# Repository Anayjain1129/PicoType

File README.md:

# PicoType 

## Zine Page

## Physically Built

### What is this project? 
This is a keyboard made from scratch made by a teenage, made from PCB, CAD to firmware everything! basically this is a keyboard which helps you type things and uses RP2040 and and it sounds thockyy!! 

### How to use it?
1. Assemble the PCB by soldering the Raspberry pi pico, switches and encoder and the OLED display which is on the numpad pcb
2. Plug the MCU (raspberry pi pico) with your computer and make sure the boot button on the MCU is pressed down while you are plugging in the MCU
3. Drag and drop the .uf2 file in the MCU of Raspberry Pi Pico 
4. Do the same things with Xiao rp2040
5. wolla you have everything working!! 

### Why did i made this? 
I made this to learn new skills and learn more about PCBs and do ALOT of CAD the case/CAD of this project took so much time! and the case makes it looks so much awesome! and i have made a separate numpad which can alsop be used as a macropad, you can use it as a full sized keyboard or just as a ANSI-75 Keyboard with a small macropad on your desk! the numpad also have a keychian holder so you can carry it easily too! 

# Features
- EC11 Rotary Encoder - For Volume, Brightness etc
- Oled screen -  To play gifs and notifications
- ANSI-75 Layout
- Raspberry Pi Pico
- Custom Layout
- QMK firmware
- Awesome CAD/cool case design
- Uses RP2040

## Schematics 

## PCB

## 3d PCB

# Case
## Top

## Middle Plate

## Bottom

# 3d view of all parts together

# BOM
| # | Item | Description | Quantity | URL | Total Price (INR) | Total Price (USD) |
|---|------|-------------|----------|-----|:-----------------:|:-----------------:|
| 1 | Numpad PCB | PCB for the Numpad | 5 | N/A | ₹1,845 | $19.53 |
| 2 | PicoType PCB | PCB for the PicoType | 5 | N/A | ₹5,175 | $54.67 |
| 3 | 0.91 Inch OLED | OLED display | 1 | [Link](https://robu.in/product/blue-oled-display-module/) | ₹151 | $1.60 |
| 4 | Switches | The mechanical switches | 11 | [Link](https://neomacro.in/products/gateron-ef-cedar) | ₹1,980 | $20.92 |
| 5 | Rotary Encoder | The Rotary Encoder which can | 1 | [Link](https://robu.in/product/hongyan-ec11h-7ce20p1zy15f7-rotary-encoder-with-push-button-switch-vertical-plug-in-5-pin/) | ₹55 | $0.58 |
| 6 | XIAO RP2040 | MCU to be used for Numpad | 1 | [Link](https://robocraze.com/products/seeed-studio-seeeduino-xiao-samd21-arduino-compatible-board) | ₹645 | $6.81 |
| 7 | Raspberry Pi Pico | MCU to be used for PicoType | 1 | [Link](https://robocraze.com/products/raspberry-pi-pico-h-pico-with-headers-soldered) | ₹525 | $5.55 |
| 8 | Keycaps | Keycaps to put on top of switches | 9 | Self Sourced | N/A | N/A |
| 9 | Case | To put everything together | 1 | Print-Legion | N/A | N/A |
| 10 | Magnets | Magnets to hold the case together | N/A | Self Sourced | N/A | N/A |
| | | | | **Total Cost** | **₹10,376** | **$109.66** |

# Demo Link
https://youtu.be/6P1yl1J2G_w?si=dBfJKUdtHREIIz_N

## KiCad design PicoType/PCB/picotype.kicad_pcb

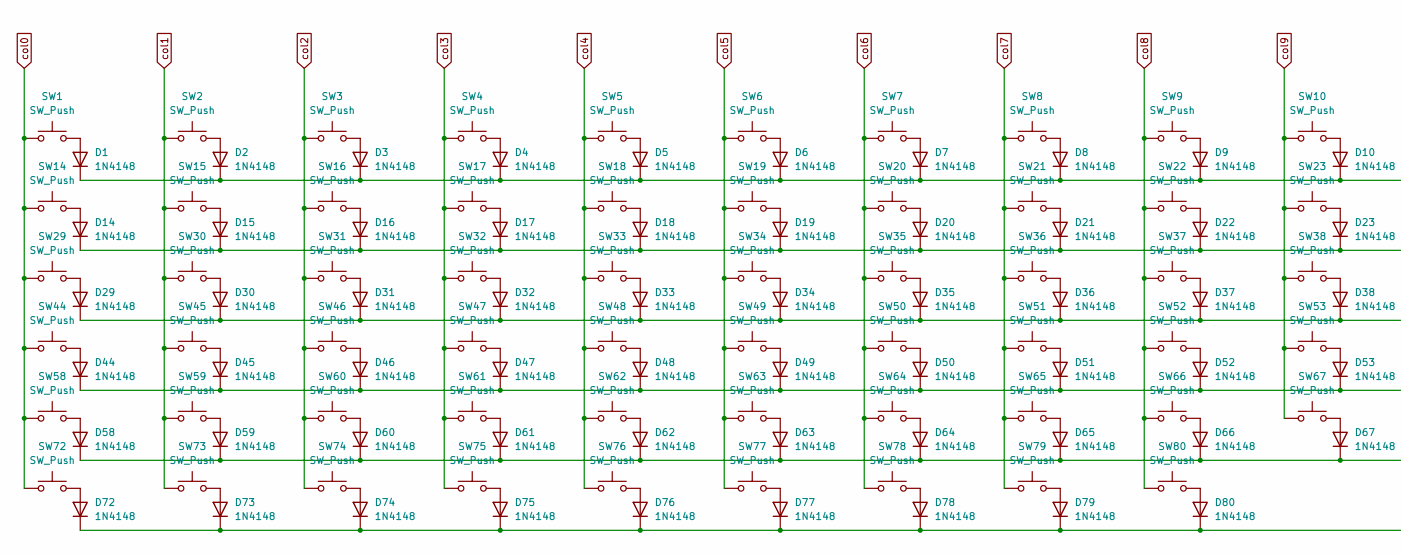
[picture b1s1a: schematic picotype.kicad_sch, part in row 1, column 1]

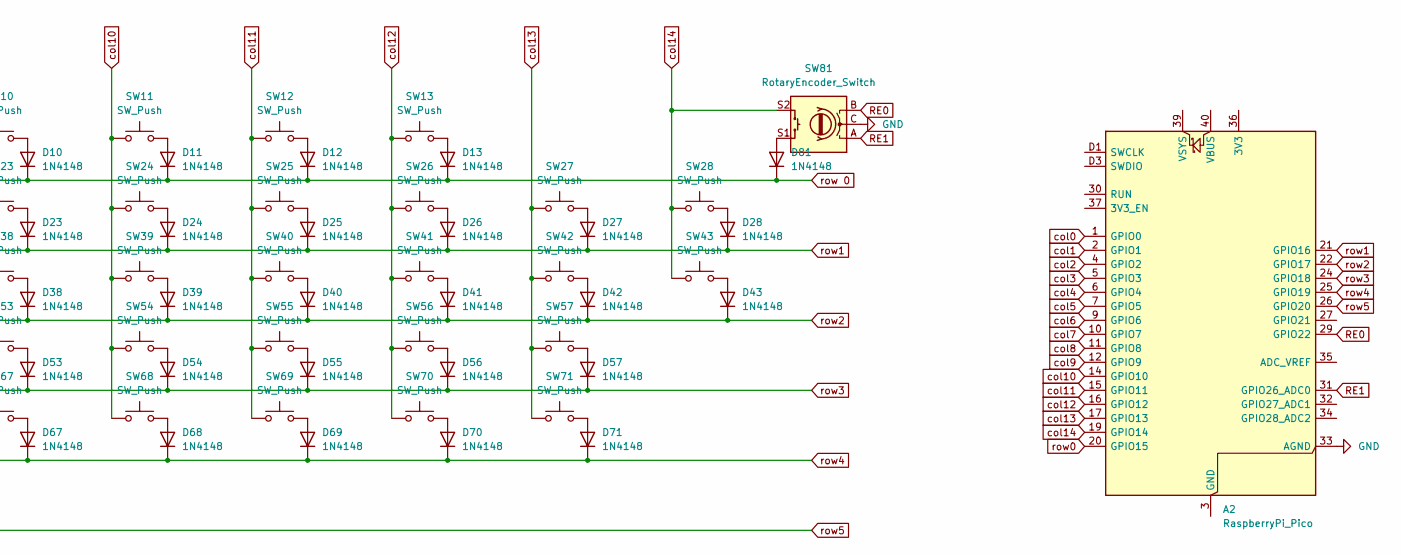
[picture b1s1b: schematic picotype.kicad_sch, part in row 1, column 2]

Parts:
A2: RaspberryPi_Pico; RaspberryPi_Pico_SMD_HandSolder
D1, D2, D3, D4, D5, D6, D7, D8, D9, D10, D11, D12, D13, D14, D15, D16, D17, D18, D19, D20, D21, D22, D23, D24, D25, D26, D27, D28, D29, D30, D31, D32, D33, D34, D35, D36, D37, D38, D39, D40, D41, D42, D43, D44, D45, D46, D47, D48, D49, D50, D51, D52, D53, D54, D55, D56, D57, D58, D59, D60, D61, D62, D63, D64, D65, D66, D67, D68, D69, D70, D71, D72, D73, D74, D75, D76, D77, D78, D79, D80, D81: 1N4148; D_DO-35_SOD27_P7.62mm_Horizontal
SW1, SW2, SW3, SW4, SW5, SW6, SW7, SW8, SW9, SW10, SW11, SW12, SW13, SW14, SW15, SW16, SW17, SW18, SW19, SW20, SW21, SW22, SW23, SW24, SW25, SW26, SW28, SW30, SW31, SW32, SW33, SW34, SW35, SW36, SW37, SW38, SW39, SW40, SW41, SW43, SW45, SW46, SW47, SW48, SW49, SW50, SW51, SW52, SW53, SW54, SW55, SW57, SW59, SW60, SW61, SW62, SW63, SW64, SW65, SW66, SW67, SW68, SW70, SW71, SW78, SW79, SW80: SW_Push; SW_Cherry_MX_1.00u_PCB
SW27: SW_Push; SW_Cherry_MX_2.00u_PCB
SW29, SW42: SW_Push; SW_Cherry_MX_1.50u_PCB
SW44, SW69: SW_Push; SW_Cherry_MX_1.75u_PCB
SW56, SW58: SW_Push; SW_Cherry_MX_2.25u_PCB
SW72, SW73, SW74, SW76, SW77: SW_Push; SW_Cherry_MX_1.25u_PCB
SW75: SW_Push; SW_Cherry_MX_6.25u_PCB
SW81: RotaryEncoder_Switch; RotaryEncoder_Alps_EC12E-Switch_Vertical_H20mm_CircularMoun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

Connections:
GND: A2.33 (AGND), SW81.C
unnamed: A2.3 (GND), A2.8 (GND), A2.13 (GND), A2.18 (GND), A2.23 (GND), A2.28 (GND), A2.38 (GND), A2.D2 (GND)
unnamed: D1.2 (A), SW1.2
unnamed: D2.2 (A), SW2.2
unnamed: D3.2 (A), SW3.2
unnamed: D4.2 (A), SW4.2
unnamed: D5.2 (A), SW5.2
unnamed: D6.2 (A), SW6.2
unnamed: D7.2 (A), SW7.2
unnamed: D8.2 (A), SW8.2
unnamed: D9.2 (A), SW9.2
unnamed: D10.2 (A), SW10.2
unnamed: D11.2 (A), SW11.2
unnamed: D12.2 (A), SW12.2
unnamed: D13.2 (A), SW13.2
unnamed: D14.2 (A), SW14.2
unnamed: D15.2 (A), SW15.2
unnamed: D16.2 (A), SW16.2
unnamed: D17.2 (A), SW17.2
unnamed: D18.2 (A), SW18.2
unnamed: D19.2 (A), SW19.2
unnamed: D20.2 (A), SW20.2
unnamed: D21.2 (A), SW21.2
unnamed: D22.2 (A), SW22.2
unnamed: D23.2 (A), SW23.2
unnamed: D24.2 (A), SW24.2
unnamed: D25.2 (A), SW25.2
unnamed: D26.2 (A), SW26.2
unnamed: D27.2 (A), SW27.2
unnamed: D28.2 (A), SW28.2
unnamed: D29.2 (A), SW29.2
unnamed: D30.2 (A), SW30.2
unnamed: D31.2 (A), SW31.2
unnamed: D32.2 (A), SW32.2
unnamed: D33.2 (A), SW33.2
unnamed: D34.2 (A), SW34.2
unnamed: D35.2 (A), SW35.2
unnamed: D36.2 (A), SW36.2
unnamed: D37.2 (A), SW37.2
unnamed: D38.2 (A), SW38.2
unnamed: D39.2 (A), SW39.2
unnamed: D40.2 (A), SW40.2
unnamed: D41.2 (A), SW41.2
unnamed: D42.2 (A), SW42.2
unnamed: D43.2 (A), SW43.2
unnamed: D44.2 (A), SW44.2
unnamed: D45.2 (A), SW45.2
unnamed: D46.2 (A), SW46.2
unnamed: D47.2 (A), SW47.2
unnamed: D48.2 (A), SW48.2
unnamed: D49.2 (A), SW49.2
unnamed: D50.2 (A), SW50.2
unnamed: D51.2 (A), SW51.2
unnamed: D52.2 (A), SW52.2
unnamed: D53.2 (A), SW53.2
unnamed: D54.2 (A), SW54.2
unnamed: D55.2 (A), SW55.2
unnamed: D56.2 (A), SW56.2
unnamed: D57.2 (A), SW57.2
unnamed: D58.2 (A), SW58.2
unnamed: D59.2 (A), SW59.2
unnamed: D60.2 (A), SW60.2
unnamed: D61.2 (A), SW61.2
unnamed: D62.2 (A), SW62.2
unnamed: D63.2 (A), SW63.2
unnamed: D64.2 (A), SW64.2
unnamed: D65.2 (A), SW65.2
unnamed: D66.2 (A), SW66.2
unnamed: D67.2 (A), SW67.2
unnamed: D68.2 (A), SW68.2
unnamed: D69.2 (A), SW69.2
unnamed: D70.2 (A), SW70.2
unnamed: D71.2 (A), SW71.2
unnamed: D72.2 (A), SW72.2
unnamed: D73.2 (A), SW73.2
unnamed: D74.2 (A), SW74.2
unnamed: D75.2 (A), SW75.2
unnamed: D76.2 (A), SW76.2
unnamed: D77.2 (A), SW77.2
unnamed: D78.2 (A), SW78.2
unnamed: D79.2 (A), SW79.2
unnamed: D80.2 (A), SW80.2
unnamed: D81.2 (A), SW81.S1
RE0: A2.29 (GPIO22), SW81.B
RE1: A2.31 (GPIO26_ADC0), SW81.A
col0: A2.1 (GPIO0), SW1.1, SW14.1, SW29.1, SW44.1, SW58.1, SW72.1
col1: A2.2 (GPIO1), SW2.1, SW15.1, SW30.1, SW45.1, SW59.1, SW73.1
col2: A2.4 (GPIO2), SW3.1, SW16.1, SW31.1, SW46.1, SW60.1, SW74.1
col3: A2.5 (GPIO3), SW4.1, SW17.1, SW32.1, SW47.1, SW61.1, SW75.1
col4: A2.6 (GPIO4), SW5.1, SW18.1, SW33.1, SW48.1, SW62.1, SW76.1
col5: A2.7 (GPIO5), SW6.1, SW19.1, SW34.1, SW49.1, SW63.1, SW77.1
col6: A2.9 (GPIO6), SW7.1, SW20.1, SW35.1, SW50.1, SW64.1, SW78.1
col7: A2.10 (GPIO7), SW8.1, SW21.1, SW36.1, SW51.1, SW65.1, SW79.1
col8: A2.11 (GPIO8), SW9.1, SW22.1, SW37.1, SW52.1, SW66.1, SW80.1
col9: A2.12 (GPIO9), SW10.1, SW23.1, SW38.1, SW53.1, SW67.1
col10: A2.14 (GPIO10), SW11.1, SW24.1, SW39.1, SW54.1, SW68.1
col11: A2.15 (GPIO11), SW12.1, SW25.1, SW40.1, SW55.1, SW69.1
col12: A2.16 (GPIO12), SW13.1, SW26.1, SW41.1, SW56.1, SW70.1
col13: A2.17 (GPIO13), SW27.1, SW42.1, SW57.1, SW71.1
col14: A2.19 (GPIO14), SW28.1, SW43.1, SW81.S2
row0: A2.20 (GPIO15)
row1: A2.21 (GPIO16), D14.1 (K), D15.1 (K), D16.1 (K), D17.1 (K), D18.1 (K), D19.1 (K), D20.1 (K), D21.1 (K), D22.1 (K), D23.1 (K), D24.1 (K), D25.1 (K), D26.1 (K), D27.1 (K), D28.1 (K)
row2: A2.22 (GPIO17), D29.1 (K), D30.1 (K), D31.1 (K), D32.1 (K), D33.1 (K), D34.1 (K), D35.1 (K), D36.1 (K), D37.1 (K), D38.1 (K), D39.1 (K), D40.1 (K), D41.1 (K), D42.1 (K), D43.1 (K)
row3: A2.24 (GPIO18), D44.1 (K), D45.1 (K), D46.1 (K), D47.1 (K), D48.1 (K), D49.1 (K), D50.1 (K), D51.1 (K), D52.1 (K), D53.1 (K), D54.1 (K), D55.1 (K), D56.1 (K), D57.1 (K)
row4: A2.25 (GPIO19), D58.1 (K), D59.1 (K), D60.1 (K), D61.1 (K), D62.1 (K), D63.1 (K), D64.1 (K), D65.1 (K), D66.1 (K), D67.1 (K), D68.1 (K), D69.1 (K), D70.1 (K), D71.1 (K)
row5: A2.26 (GPIO20), D72.1 (K), D73.1 (K), D74.1 (K), D75.1 (K), D76.1 (K), D77.1 (K), D78.1 (K), D79.1 (K), D80.1 (K)
row 0: D1.1 (K), D2.1 (K), D3.1 (K), D4.1 (K), D5.1 (K), D6.1 (K), D7.1 (K), D8.1 (K), D9.1 (K), D10.1 (K), D11.1 (K), D12.1 (K), D13.1 (K), D81.1 (K)

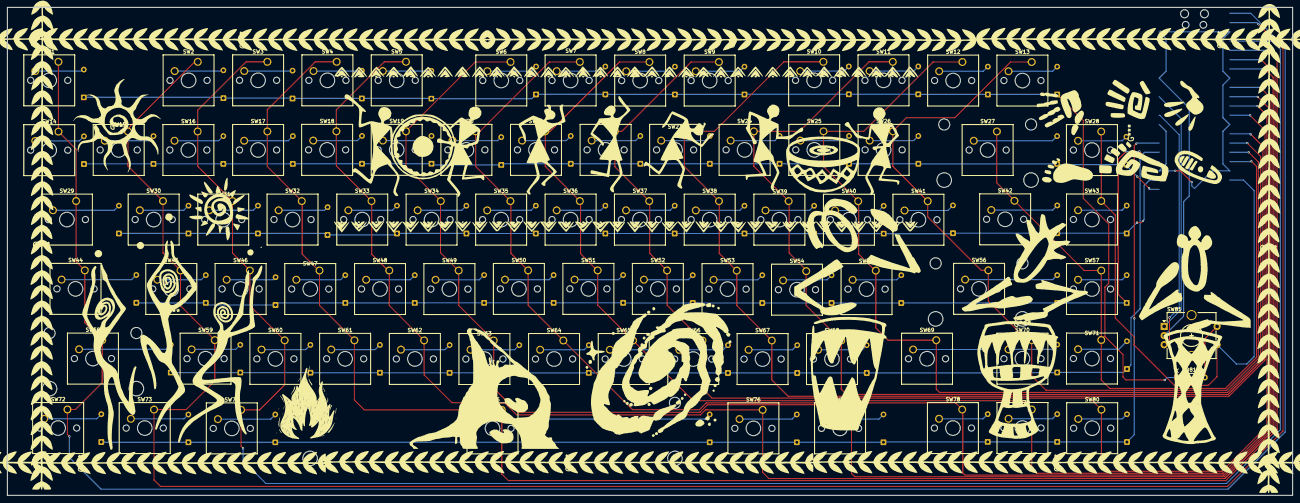
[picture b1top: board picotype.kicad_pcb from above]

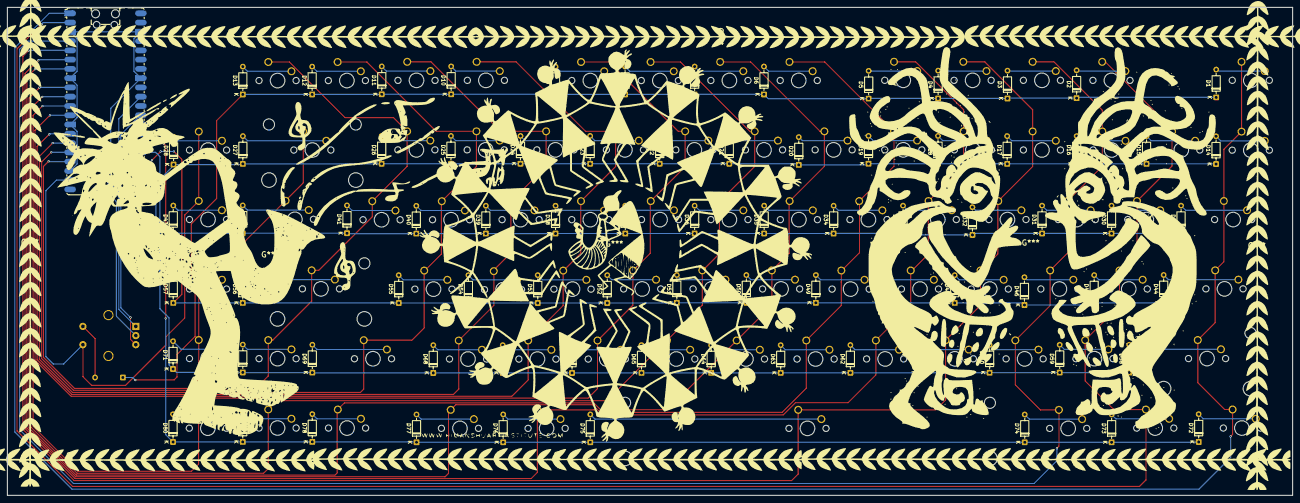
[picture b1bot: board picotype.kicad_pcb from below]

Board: 2 copper layers, 352.2 x 133.7 mm, 163 parts (81 on the bottom side), 106 nets.

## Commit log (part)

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2026-06-14 Fix project name and add screenshot to README
2026-06-14 Enhance README with project details and images
    Added detailed project description, features, and images.
2026-06-14 Fix image formatting in README.md
2026-06-16 Add Zine Page section to README
    Added a new section for 'Zine Page' with an image.
